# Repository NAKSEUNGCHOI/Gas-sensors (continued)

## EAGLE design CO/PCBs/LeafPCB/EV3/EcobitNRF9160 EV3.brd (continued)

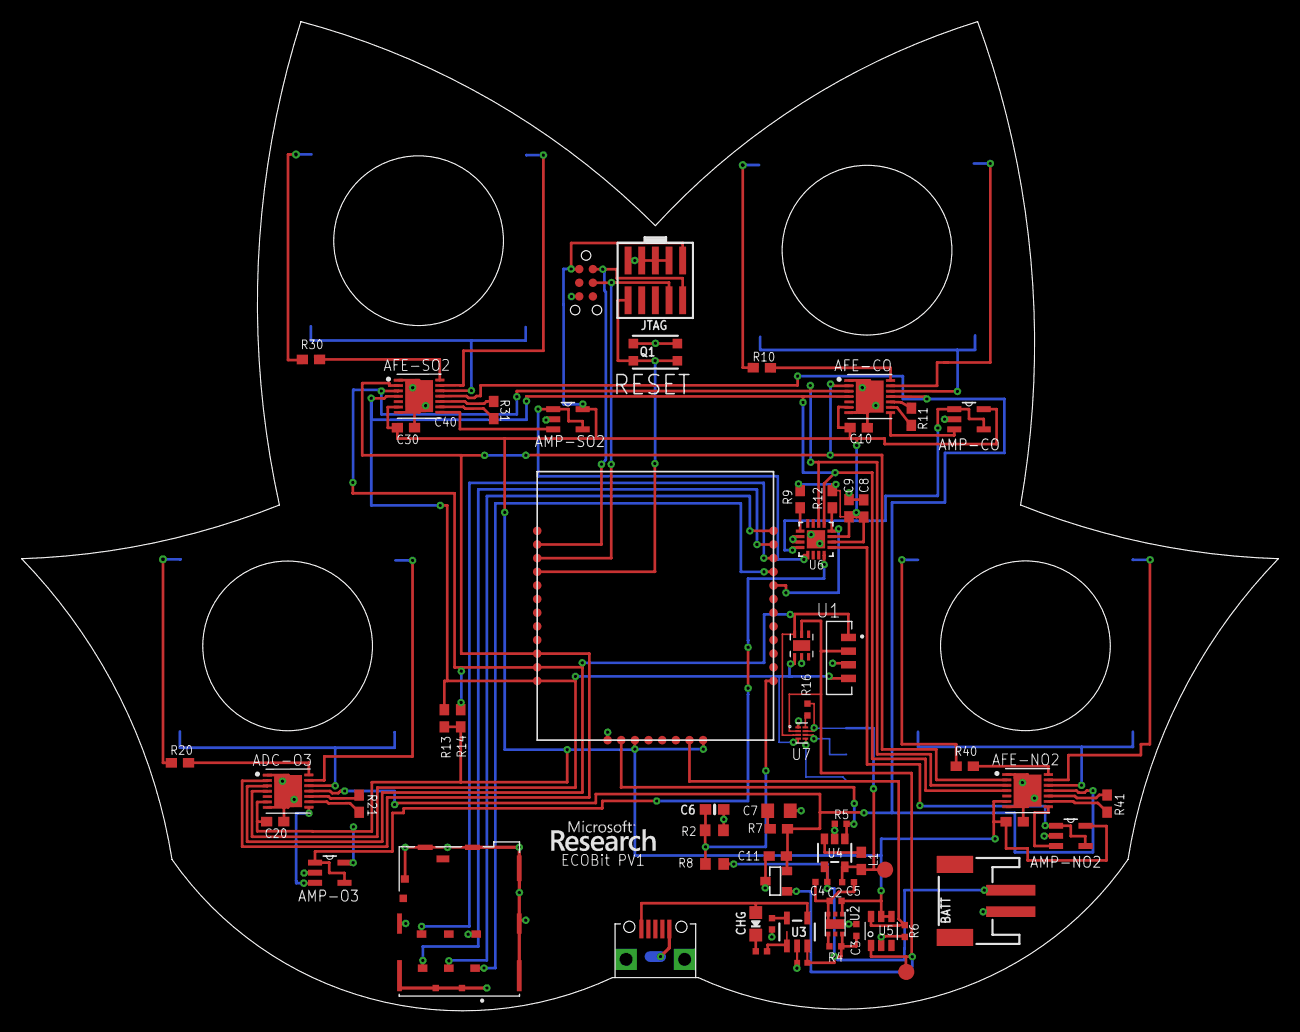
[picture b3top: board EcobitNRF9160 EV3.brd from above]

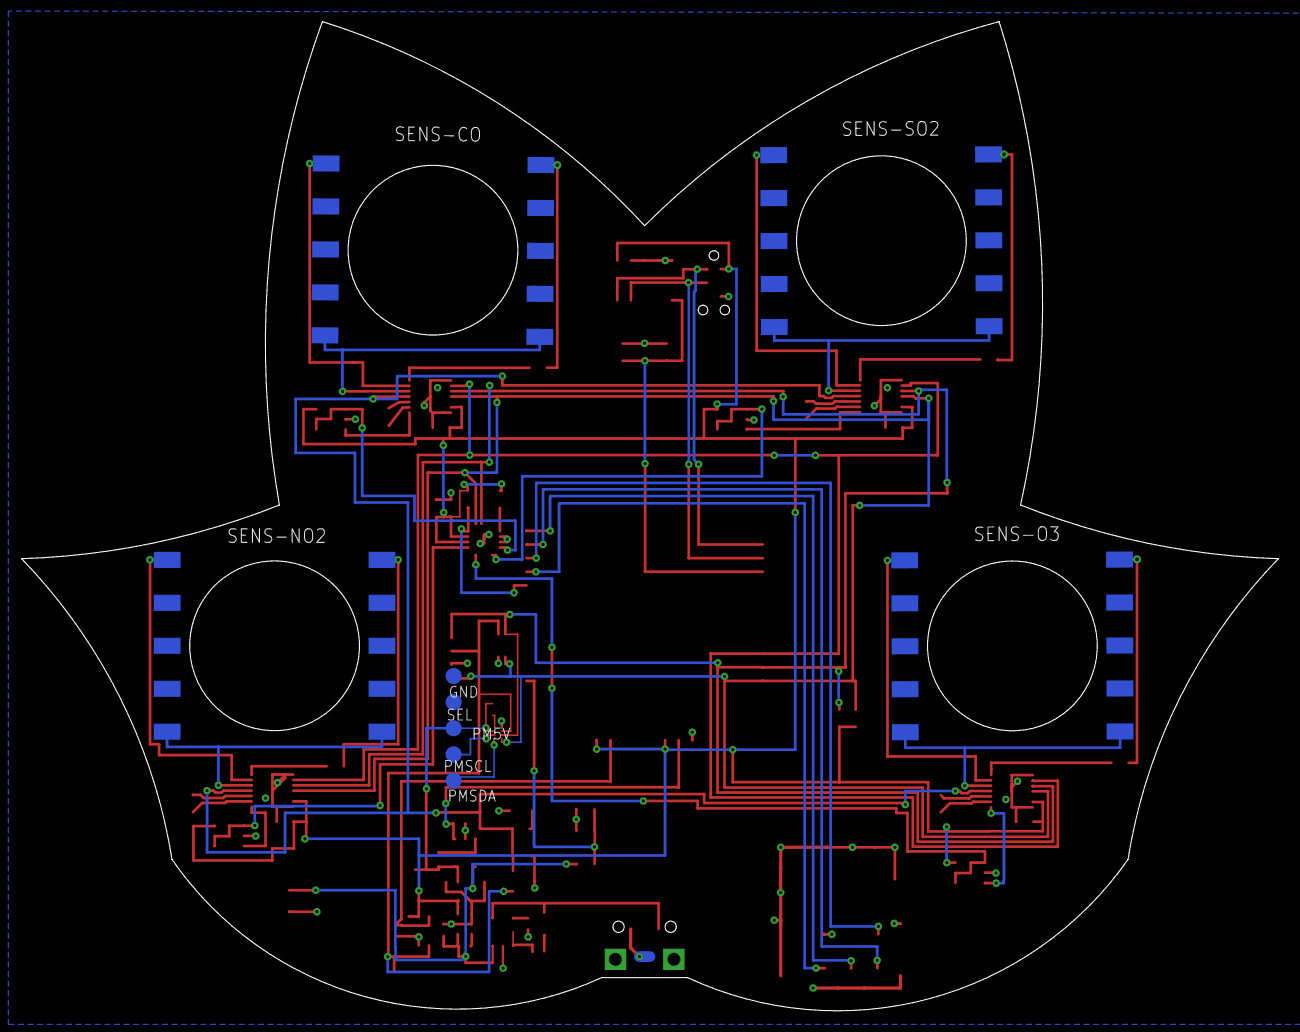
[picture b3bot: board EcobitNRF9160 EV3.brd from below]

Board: 2 copper layers, 117.0 x 92.1 mm, 72 parts (9 on the bottom side), 63 nets.

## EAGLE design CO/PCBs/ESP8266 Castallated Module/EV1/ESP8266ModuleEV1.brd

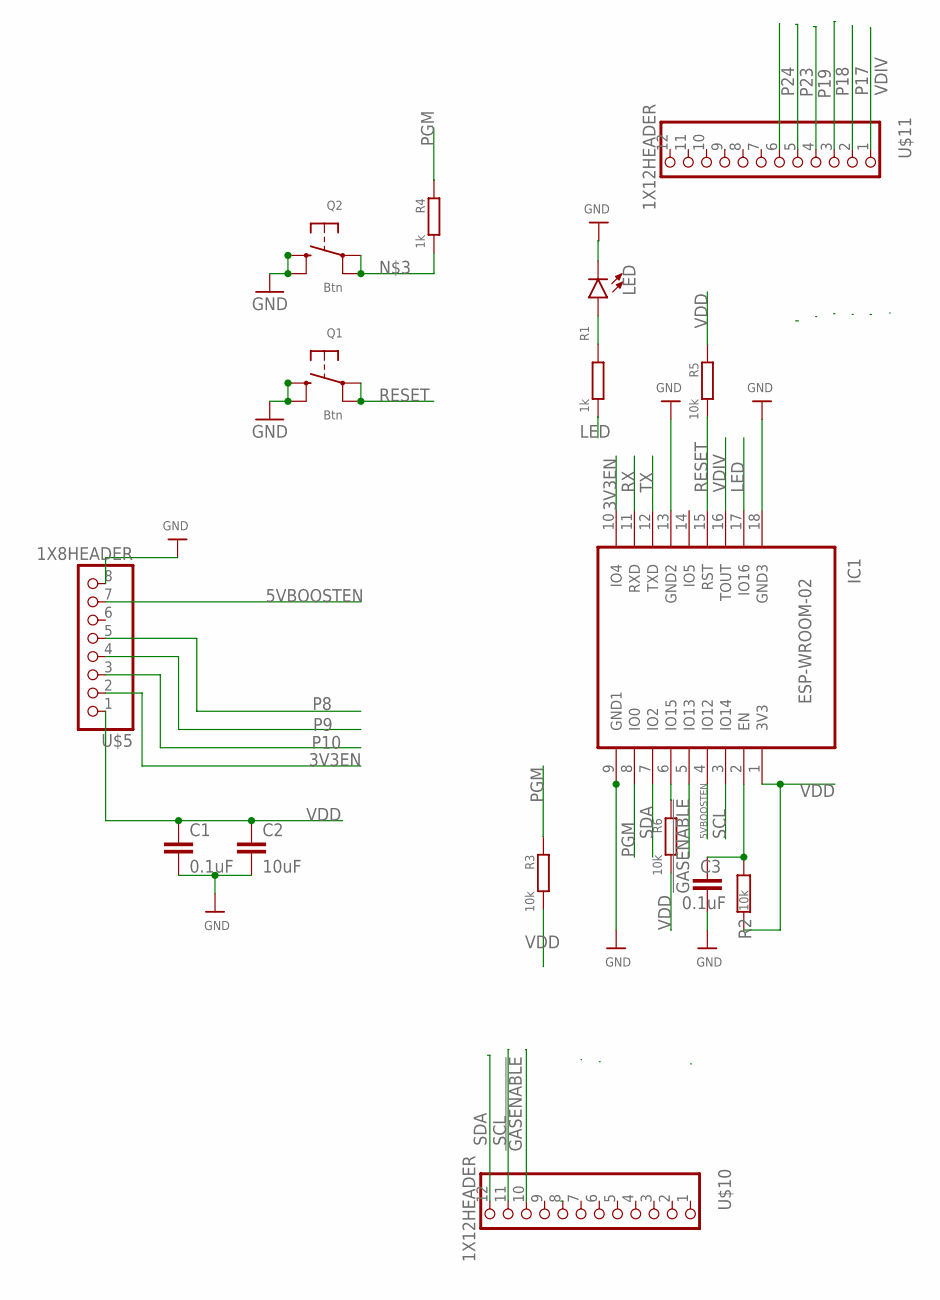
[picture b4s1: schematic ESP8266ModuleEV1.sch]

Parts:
C1, C3: 0.1uF; RESC0402_N
C2: 10uF; RESC0402_N
IC1: ESP-WROOM-02
LED: LED0603; LED-0603
Q1, Q2: Btn; BTN_KMR2_4.6X2.8
R1, R4: 1k; R0402
R2: 10k; RESC0402_N
R3, R5, R6: 10k; R0402
U$5: 1X8HEADER; 8X1
U$10, U$11: 1X12HEADER; 1X12

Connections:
3V3EN: IC1.10 (IO4), U$5.2
5VBOOSTEN: IC1.4 (IO12), U$5.7
!GASENABLE: IC1.5 (IO13), U$10.10
GND: C1.2, C2.2, C3.2, IC1.9 (GND1), IC1.13 (GND2), IC1.18 (GND3), IC1.19 (GND0), LED.C, Q1.B (S), Q1.B' (S1), Q2.B (S), Q2.B' (S1), U$5.8
LED: IC1.17 (IO16), R1.2
unnamed: C3.1, IC1.2 (EN), R2.2
unnamed: IC1.6 (IO15), R6.1
unnamed: Q2.A, Q2.A' (P1), R4.2
unnamed: LED.A, R1.1
P8: U$5.5
P9: U$5.4
P10: U$5.3
P17: U$11.2
P18: U$11.3
P19: U$11.4
P23: U$11.5
P24: U$11.6
P29: U$10.8
PGM: IC1.8 (IO0), R3.1, R4.1
RESET: IC1.15 (RST), Q1.A, Q1.A' (P1), R5.2
RX: IC1.11 (RXD)
SCL: IC1.3 (IO14), U$10.11
SDA: IC1.7 (IO2), U$10.12
SIM1V8: U$11.9
TX: IC1.12 (TXD)
VDD: C1.1, C2.1, IC1.1 (3V3), R2.1, R3.2, R5.1, R6.2, U$5.1
VDIV: IC1.16 (TOUT), U$11.1

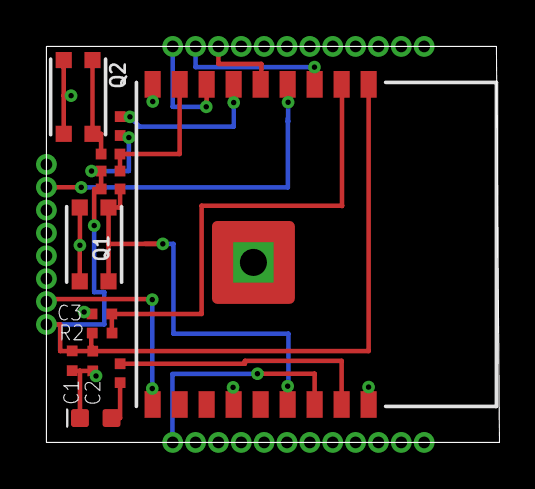
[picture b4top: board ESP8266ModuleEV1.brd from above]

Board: 2 copper layers, 25.2 x 22.0 mm, 16 parts (0 on the bottom side), 15 nets.

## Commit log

2022-07-28 CO Sensor PCB Design
2022-08-03 New CO PCB Design
2022-08-03 new pcb design for CO
2022-08-03 NEW PCB DESIGN
2022-08-08 noted
2022-08-09 debugging
2022-09-02 pulling
